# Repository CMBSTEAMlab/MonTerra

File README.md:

# MonTerra Soil Moisture Monitoring Station Manual

## Overview

### About the MonTerra Soil Moisture Monitoring Station

The Children’s Museum of Bozeman’s STEAMlab is a hands-on, mentor-led learning environment where children from a wide variety of backgrounds and skill levels combine digital design, high-tech fabrication and simple electronics to construct meaningful projects, build skills, and unlock understanding.

In partnership with Montana State University’s Extended University and the Institute on Ecosystems, students in the STEAMlab engaged in a year-long project to design, prototype and test a variety of tools for measuring soil moisture. Each component of the MonTerra Soil Moisture Monitoring Station - from the 3D printed enclosure to the interior circuitry to the code that uploads moisture data to the web - was designed by high school kids in Bozeman for use by schoolchildren all around Montana.

The MonTerra Development Team is overseen by John Allwine and Richard Harjes of the Children’s Museum of Bozeman STEAMlab. Team members are Henry Barker, Gabriel Brokaw, Lucas Kearns, Owen Mitchell, Nic Rust, Harry Schwem, Ren Wall and Yufu Yoshimura.

### Measuring soil moisture with your MonTerra Soil Moisture Monitoring Station

#### What is soil moisture

Soil moisture is the water that is held in the spaces between soil particles. This moisture can enter the soil through surface precipitation - like rain and snow - and can also be absorbed from the surrounding soil, as water migrates to fill empty spaces between soil particles. Water can leave the soil through evaporation, as well as through drainage. Different types of soil absorb and retain moisture at different rates.

Many valuable nutrients are dissolved in this water, and are carried from one area of the soil to another. Water makes chemical reactions in the soil possible, and supplies microorganisms with the elements necessary for life.

#### Why is measuring soil moisture important?

Measuring the amount of water contained in soil yields valuable information that can be used to identify trends in plant health, local crop conditions, long-term weather patterns, and even global climate. Farmers, scientists, engineers, government agencies and private companies are all interested in data about soil moisture.

#### How does the MonTerra Soil Moisture Monitoring Station work?

The MonTerra uses a “capacitive” sensor, which measures the ability of a material (in this case, soil) to hold an electrical charge when a voltage is applied to it. The sensor in the MonTerra is the tiny purple circuit board at the end of the long wire that is attached to the Arduino controller inside the 3D printed housing. It will need to be carefully buried in the soil at a depth of 12 inches in order to function properly. The MonTerra is powered by six NiMH rechargeable batteries.

The Arduino controller acts as the “brain” of the MonTerra. The Arduino contains a tiny computer chip that can be programmed using the Arduino Integrated Development Environment (or IDE) to perform a wide variety of tasks. We’ve programmed the MonTerra’s Arduino to send an electrical current through the sensor that you’ve buried in the ground. The sensor contains two copper plates that work together to measure the amount of electrical charge that is held in the soil. The Arduino determines this charge by measuring how long it takes for voltage to travel from its “send” pin, through the sensor, and back to its “receive” pin. This measurement is directly related to the amount of water contained in the soil. If you hold the capacitor in the air, it returns a number to the Arduino between 8,000 and 9,000. If you place the capacitor in a glass or water, the number is closer to 100,000. So the higher the number, the more moisture is contained in the soil.

Touchscreens on iPads and smartphones use this exact same system to record the movements of your finger. Human skin is about 70% water. When your finger comes into contact with the touch screen, the screen measures the change in capacitance from low (air) to high (finger), and uses that data to determine your finger’s location.

The Arduino “brain” also uploads the sensor data to the wifi chip, and controls the sensor’s cycle of sleep/wakefulness. All of these activities are determined in the code (the computer program) that we’ve written for the Arduino. In order to get your MonTerra up and running, you’ll need to modify the code to connect it to your school’s wifi account. See below for instructions.

You can also modify the code to make other changes to the MonTerra, for example, to increase the number of measurements that the sensor records, add additional sensors, connect it to external devices, etc. You could code the MonTerra to run an automatic watering system for a houseplant or greenhouse; you could program it to communicate with other sensors to irrigate an entire farm.

### Components

The soil moisture monitoring station is composed of the following components:

#### MonTerra Soil Moisture Monitoring Board

This purple printed circuit board (PCB) has sockets for several of the components listed below and the necessary connections between them so that they can function as a soil moisture monitoring station. The modular design allows for easy removal and replacement of faulty components. It also allows for the use of the Arduino and XBee module in other projects.

#### Arduino - Pololu A-Star 32U4 Mini LV

This Arduino-compatible microcontroller was chosen for its efficient power regulator, which allows it to be powered from any power source between 2.7 and 11.8 volts. Other models of the Pololu A-Star 32U4 family have the same footprint and can be interchanged. The ULV model supports voltages from .5V to 5.5V and the SV model supports 5V to 36V. Having this flexibility allows for different battery configurations so further development can be made (such as designing for a solar charging station).

#### XBee Wifi Module

This module transmits the soil moisture data to the cloud. There are other kinds of XBee modules that could be interchanged to transfer data in different ways (such as point to point or mesh networks).

#### Bidirectional 3.3V to 5V level shifter

The Arduino runs at 5V, whereas the XBee module runs at 3.3V so to communicate with each other the voltage needs to be converted from one to the other.

#### MonTerra Soil Moisture Sensor

The sensor uses capacitive plates that can sense changes to the material surrounding it (called the dielectric). The plates in the sensor form a capacitor and it works by seeing how long it takes for the capacitor to charge. Wet soil takes longer to charge than dry soil.

#### Batteries

The MonTerra is powered using 6 NiMH rechargeable AA batteries, which provide a nominal voltage of 7.2V. The batteries will need to be charged weekly during standard deployment. The batteries should not be recharged at temperatures below 32 degrees Fahrenheit. If the batteries are cold, bring them indoors and allow them to come up to room temperature before recharging.

#### Enclosure

Your enclosure is either a white 3D printed enclosure mounted on a metal stake or a gray electrical box that will house all of the MonTerra’s electrical components.

## Setup

### Arduino IDE

1. Download Arduino IDE - https://www.arduino.cc/en/Main/Software
2. Install the Arduino IDE - https://learn.sparkfun.com/tutorials/installing-arduino-ide   
3. Install Pololu drivers and Arduino IDE settings by following steps 6.1-6.2 of the following document - https://www.pololu.com/docs/0J61/all#6
4. Run the Arduino IDE
5. Select the Pololu A-Star 32U4 Board under the Tools - Board menu 
6. Select Pololu USB AVR Programmer under the Tools - Programmer menu 
7. Connect the Pololu A-Star 32U4 Mini LV to your computer with the provided USB cable.
8. Select the USB port that corresponds to the Pololu A-Star 32U4 Mini LV under the Tools - Port menu (on Windows it will be COM# with the # replaced with the port number) 

### Setup a Phant stream

1. In a browser, go to http://69.145.204.62:8080/
2. Click Create to create a data stream. 
3. Fill in the title and description to identify your monitoring station. 
4. Fill in the Fields text box with attempt, moisture, sequence and stationid (make sure the case matches exactly): 
5. Enter your location 
6. Optionally, set an alias for the stream (this can make it easier to remember the URL of your stream)
7. You will be presented with a URL and a number of keys (public, private and delete). Write these keys down or save them to a file as you’ll need to program them into your soil moisture monitoring station. 

### Configure your wifi network

1. Download the MonTerra project: https://github.com/CMBSTEAMlab/MonTerra/archive/master.zip
2. Unzip master.zip
3. Open the Arduino IDE
4. Click File - Open… and navigate arduino/MonTerra/MonTerra.ino
5. Replace <WiFi Network Name> with the name of your wifi network. 
6. Replace <WiFi Password> with your wifi network’s password. If your network is open (doesn’t require a password), remove <WiFi Password>.  
7. WPA2 is the most common authentication type, but if your network is different change WPA2 to one of NO_SECURITY, WPA, or WEP. 
8. Replace <Station ID> with a descriptive name for your soil moisture monitoring station. 
9. Replace <Phant public key> with the public key from step 7 of “Setup a Phant stream” above. 
10. Replace <Phant private key> with the private key from step 7 of “Setup a Phant stream” above. 
11. Connect the Pololu A-Star 32U4 Mini LV to your computer with the provided USB cable.
12. Click the Upload button in the upper left (
) or under the Sketch menu.
13. Wait for the the “Done uploading.” message in the lower left corner. See the troubleshooting section if you don’t see this message.

## Use Cases

### Deploy the MonTerra Soil Moisture Monitor

1. Place the soil moisture monitoring board in the enclosure and fit the cover over it, tightening all necessary screws.
2. Drive the metal stake into the ground where your soil moisture will be monitored
3. Affix the enclosure to metal stake, no more than 12 inches above the ground.
4. Carefully bury the soil moisture sensor in the ground at a depth of 12 inches.
5. Connect the battery pack to the wire inside the battery compartment. 
6. In a browser, go to the URL provided in step 7 of “Setup a Phant stream.”
7. You should see the soil moisture readings that are being transmitted from the monitoring station. The readings should be approximately in the range of 8,000-20,000.
8. The sensor reading frequency defaults to once a day and can be changed in the Arduino sketch.
9. With current default settings, the batteries will need to be recharged once a week. Batteries should not be recharged at temperatures below 32 degrees Fahrenheit, so allow the batteries to warm up to room temp before recharging.

### Indoor experimentation

In the zip file you downloaded in step 1 of the "Configure your wifi network" section, there is a simplified Arduino sketch that doesn’t use the wifi module, and doesn’t put the device to sleep to conserve energy. The sketch is useful for experimenting with the soil moisture sensor indoors. 

1. Open the Arduino IDE
2. Click File - Open… and navigate to the folder you extracted master.zip to.
3. Open the arduino/DebugSoilMoistureSensor/DebugSoilMoistureSensor.ino
4. Click the Upload button in the upper left () or under the Sketch menu.
5. Wait for the the “Done uploading.” message in the lower left corner. See the troubleshooting section if you don’t see this message.

### Advanced experimentation

The Pololu A-Star 32U4 Mini LV can be removed from the socket on the soil moisture monitoring board, and instead be plugged into a breadboard (not included). Wires (also not included) can be connected from the 9 pins shown in the images below. The pins used on the MonTerra Board are digital pins 0, 1, 6, 9, 10, and 13 along with 3V3, 5V and GND. If you want to power it with batteries, you also have to bring over BAT+ (BAT- is the same as GND).

You can now attach more inputs such as additional sensors for broadcasting more information to your Phant stream. You could also add outputs such as LEDs, servos or relays that react to the sensor information. After experimenting with different inputs and outputs, you could incorporate your changes into the MonTerra board using EAGLE CAD (see the “Further Resources” section below for more information about EAGLE CAD) and produce a new board that has your new inputs and outputs built-in.

## Troubleshooting

### My Arduino sketch won't upload

Things to check:
* If you’re using Windows, make sure you’ve installed the Pololu A-Star drivers. See step 3 of the "Arduino IDE" section above.
* Make sure you’ve properly connected the provided USB cable from your computer to the Pololu A-Star Mini.
* Make sure you’ve selected the Pololu board, programmer and port. See steps 5-8 of the "Arduino IDE" section.
* If the port doesn’t show up, the USB drivers may be installing, waiting several minutes with the Pololu plugged in may be all it takes before the port becomes available.
* Make sure no other applications are using the serial port (this is unlikely).

### Data isn't showing up on the Phant stream

Make sure you've gone through all steps in the "Setup" section.

Things to check:

* Make sure the public key and private key from your Phant stream match the ones you entered into the Arduino IDE.
* Make sure you’ve entered the correct Wifi network and password, along with the type of encryption (WPA2, NO_SECURITY, etc.).
* To help debug further follow the How To Enter Debug Mode section below.

### How to enter debug mode

1. In the Arduino IDE, open the MonTerra.ino sketch.
2. Find the following line that is commented out using two slashes (//) at the beginning of the line.
3. Remove the two slashes from the beginning of the line to uncomment it.
4. Click the Upload button in the upper left () or under the Sketch menu.
5. Wait for it to say “Done uploading.” at the bottom of the window then click the Serial Monitor button in the upper right corner () or under the Tools menu. If a red error appears near the bottom that says the port is not available, wait a few seconds and then click the Serial Monitor button again.

#### Debugging messages

Debugging information will continuously be printed out as the Arduino sends commands to the XBee Wifi module. Things to watch for:

##### “+++ Entering command mode” followed by “NOT OK”

This message indicates the Arduino is unable to communicate with the XBee. The XBee may be asleep. Try disconnecting all power to the Arduino by disconnecting the USB and batteries and then hooking them back up. If this message continues to be printed out, the XBee module may need to be replaced.

##### “Waiting to connect to wifi: FF” repeating over and over.

This message indicates that the XBee is trying to find the specified wifi network. If this message persists it may indicate that you’ve incorrectly input the network name. 

This error can also happen because we are in debug mode. The 3.3V power supply on the Arduino is responsible for regulating messaging over USB. Sometimes there isn’t enough power to be in debug mode and use the XBee. Hooking up the battery pack in addition to the USB cable can help get around this problem.

##### “Waiting to connect to wifi: 24” repeating over and over.

This message indicates that the provided wifi network password is incorrect. Check the WIFI_PSK variable at the top of the program.

##### “Waiting to connect to wifi: 41”

This message usually indicates that the XBee has successfully connected to the wifi network, but is still waiting to be assigned an IP address. This message should not print out more than a few times before successfully sending data to the cloud.

### Other questions?

Contact CMB STEAMlab at 406-522-9087, email steamlab@cmbozeman.org or file an issue on the MonTerra GitHub page: https://github.com/CMBSTEAMlab/MonTerra/issues.

## Circuit Diagrams

These diagrams were generated by EAGLE CAD, the software used to design the MonTerra soil moisture monitoring board.

## Further Resources

The soil moisture monitoring station was designed to be reprogrammable using Arduino and the interchangeable nature of XBee modules allows for different wireless communication techniques to be used. There is a wealth of knowledge online about these technologies. Here are a few places to start:

* To learn more about Arduino:
  * The official Arduino site - https://www.arduino.cc/en/Guide/HomePage
  * SparkFun - https://learn.sparkfun.com/tutorials/what-is-an-arduino      

* To learn more about the Pololu A-Star 32U4 Mini board:
  * Pololu Resources - https://www.pololu.com/product/3103/resources
  * A-Star GitHub repository - https://github.com/pololu/a-star

* To learn more about XBee:
  * Official XBee site - http://www.digi.com/lp/xbee
  * SparkFun datalogging with XBee - https://learn.sparkfun.com/tutorials/internet-datalogging-with-arduino-and-xbee-wifi

* To learn more about the libraries used in the MonTerra Arduino software:
  * CapacitiveSensor - https://github.com/PaulStoffregen/CapacitiveSensor
  * Phant - https://github.com/sparkfun/phant-arduino
  * Narcoleptic - https://code.google.com/p/narcoleptic/

* To learn more about EAGLE CAD, the software the MonTerra Board was designed in:
  * EAGLE CAD home page - http://www.cadsoftusa.com/
  * Tutorials by Jeremy Blum - http://www.jeremyblum.com/category/eagle-tutorials/

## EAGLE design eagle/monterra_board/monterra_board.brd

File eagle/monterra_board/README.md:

# MonTerra Board

These EAGLE files represent the MonTerra soil moisture monitoring station PCB. 
The design is meant to be modular so different parts can be swapped out, such
as the XBee Wifi Module for other XBees or the 3 different Pololu A-Star Minis.

# Future development

## Added capacitors to the board to help reduce noise for the XBee. 

From the XBee manual:

"Poor power supply can lead to poor radio performance, especially if the supply voltage is not kept
within tolerance or is excessively noisy. To help reduce noise, 1μF and 8.2pF capacitors are
recommended to be placed as near to pin 1 on the PCB as possible. If using a switching regulator for
your power supply, switching frequencies above 500 kHz are preferred. Power supply ripple should
be limited to a maximum 50mV peak to peak."

## Change the power source for the XBee

The XBee is currently being powered from the Pololu's 3V3 pin, which can't
supply enough current for the maximum XBee ratings and can result in unexpected
behavior from the XBee. Consider using this power regulator from Pololu: https://www.pololu.com/product/2122

## Add solar charging circuit

When trickle charging NiMH batteries (at or below C10), a charge controller
circuit can be avoided and a diode and solar panel is all that is needed. Otherwise,
a charge controller is necessary. 

## Add more sensors

Information such as temperature, CO2 levels, light levels would be of interest along
with soil moisture levels.

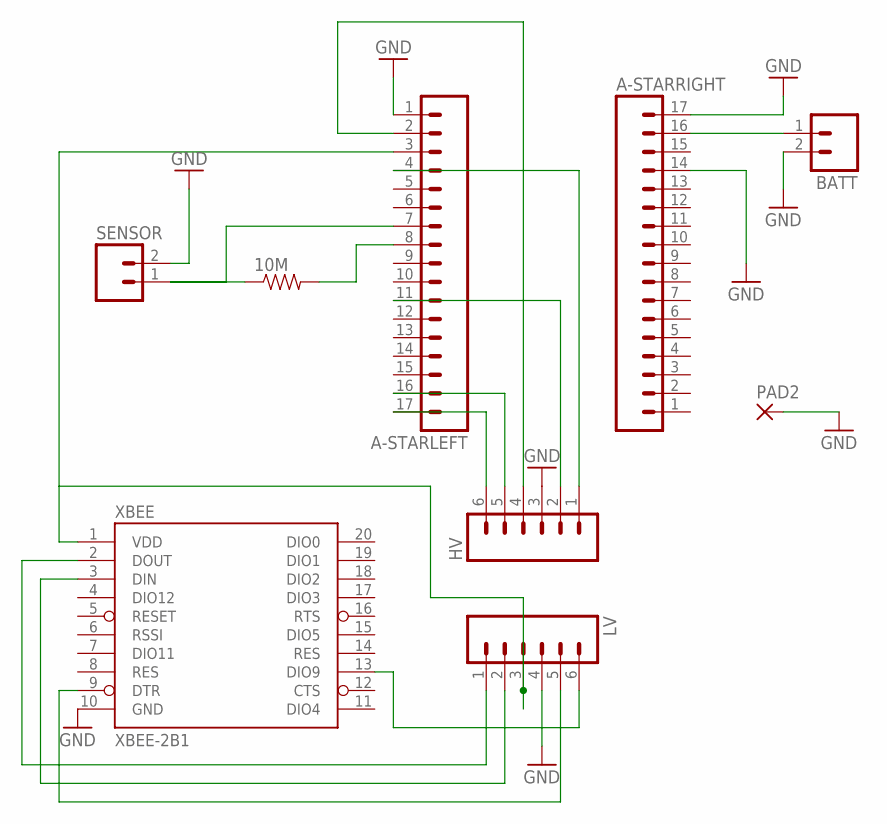
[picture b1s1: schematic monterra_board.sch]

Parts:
10M: RESISTORAXIAL-0.3; AXIAL-0.3; MPN MCF 0.25W 10M
A-STARLEFT: M17; 1X17; MPN SLW-117-01-T-S
A-STARRIGHT: M17; 1X17; MPN SLW-117-01-T-S
BATT: M02PTH; 1X02
HV: M06SILK_FEMALE_PTH; 1X06
LV: M06SILK_FEMALE_PTH; 1X06
PAD2: 3,81/1,7
SENSOR: M02PTH; 1X02
XBEE: XBEE-2B1; XBEE-1

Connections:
GND: A-STARLEFT.1, A-STARRIGHT.14, A-STARRIGHT.17, BATT.2, HV.3, LV.4, PAD2.1, SENSOR.2, XBEE.10 (GND)
unnamed: 10M.P$2 (2), A-STARLEFT.8
unnamed: 10M.P$1 (1), A-STARLEFT.7, SENSOR.1
unnamed: A-STARLEFT.2, HV.4
unnamed: A-STARLEFT.17, HV.6
unnamed: A-STARLEFT.16, HV.5
unnamed: A-STARLEFT.11, HV.2
unnamed: A-STARLEFT.4, HV.1
unnamed: A-STARRIGHT.16, BATT.1
unnamed: A-STARLEFT.3, LV.3, XBEE.1 (VDD)
unnamed: LV.1, XBEE.2 (DOUT)
unnamed: LV.2, XBEE.3 (DIN)
unnamed: LV.5, XBEE.9 (DTR)
unnamed: LV.6, XBEE.13 (DIO9)

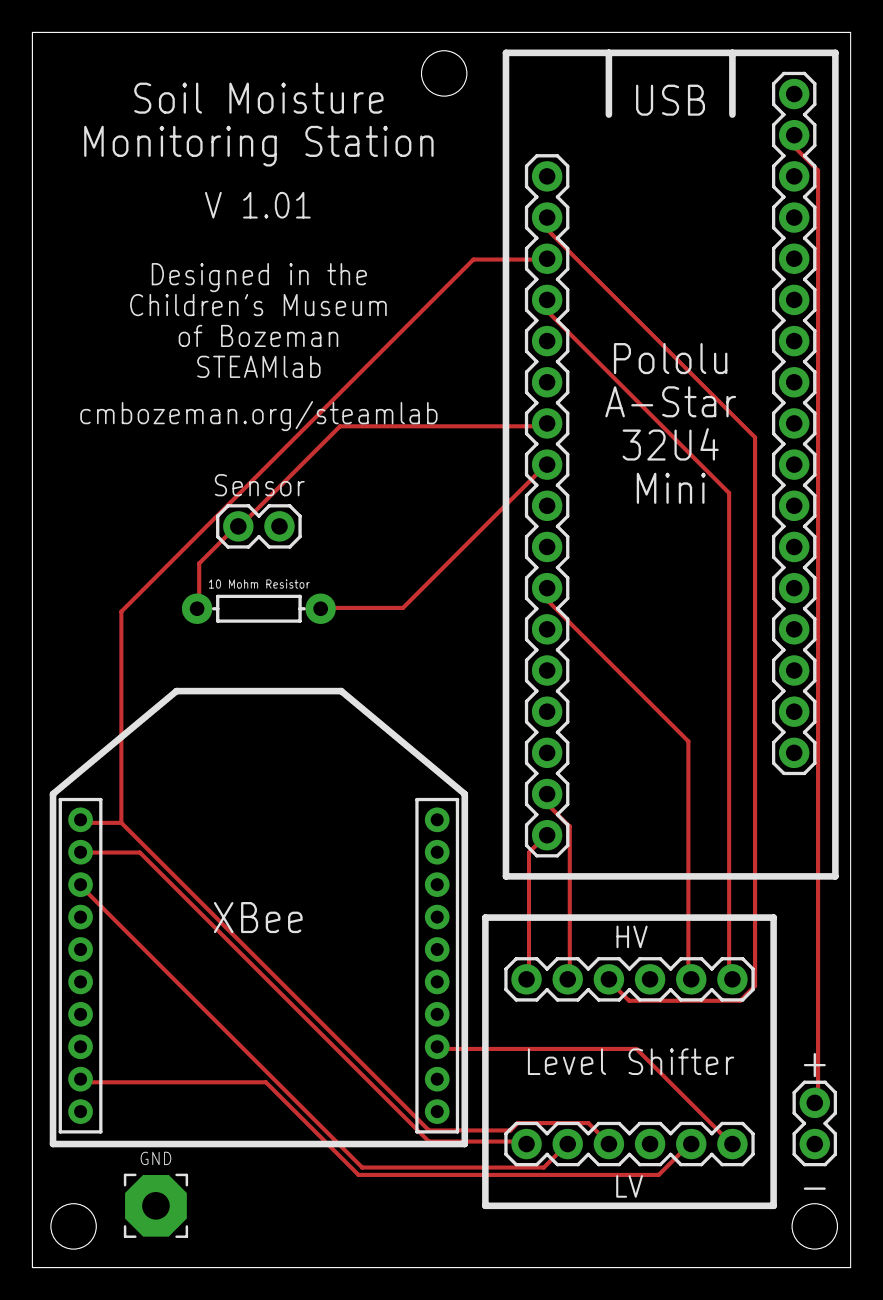
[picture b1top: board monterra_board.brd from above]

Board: 2 copper layers, 50.5 x 76.2 mm, 9 parts (0 on the bottom side), 14 nets.

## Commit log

2015-11-18 first checkin
2015-11-18 added GPL license
2015-11-20 added Capacitive Sensor library and a simple Debug sketch
2015-11-20 added some notes about the monterra board and the cap sensor
2015-11-21 updated manual, still need to add images
2015-11-21 fixed up debug section
2015-11-21 img test
2015-11-21 added more images
2015-11-21 more images
2015-11-21 changed width of images

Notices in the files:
parts and their libraries:
SparkFun-Resistors: Licensing: Creative Commons ShareAlike 4.0 International - https://creativecommons.org/licenses/by-sa/4.0
